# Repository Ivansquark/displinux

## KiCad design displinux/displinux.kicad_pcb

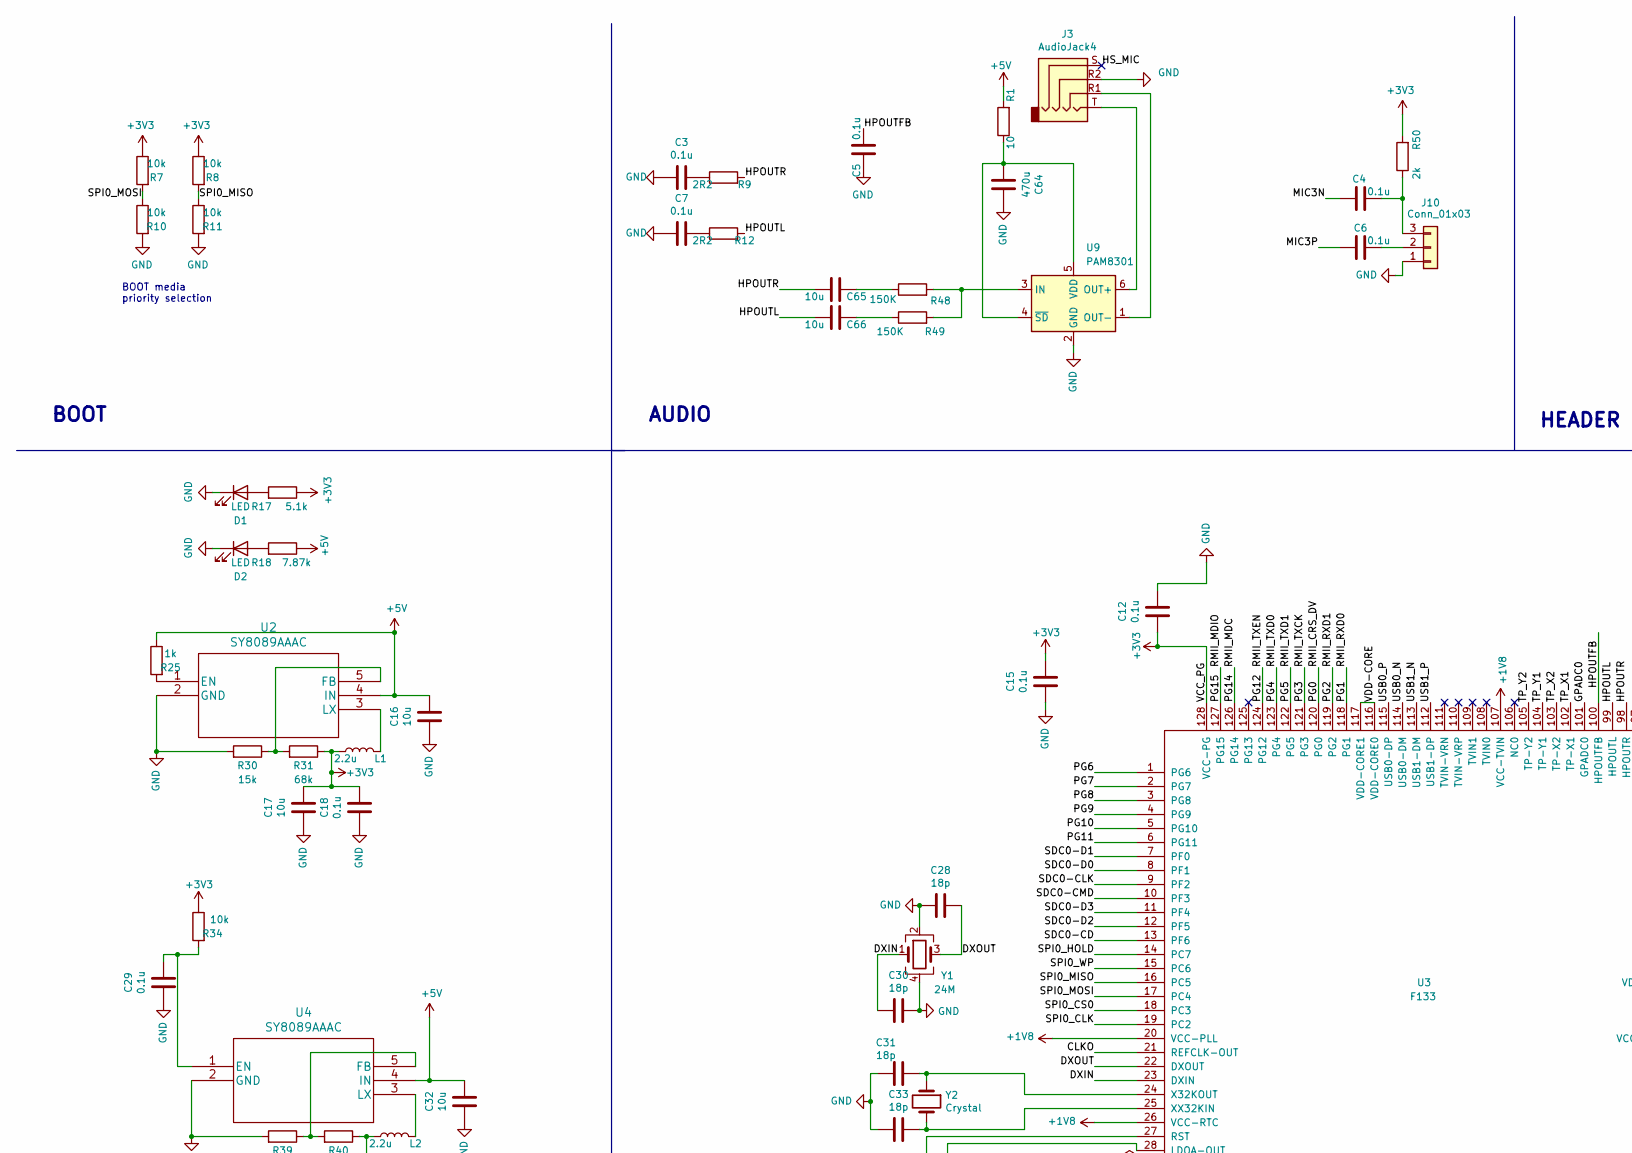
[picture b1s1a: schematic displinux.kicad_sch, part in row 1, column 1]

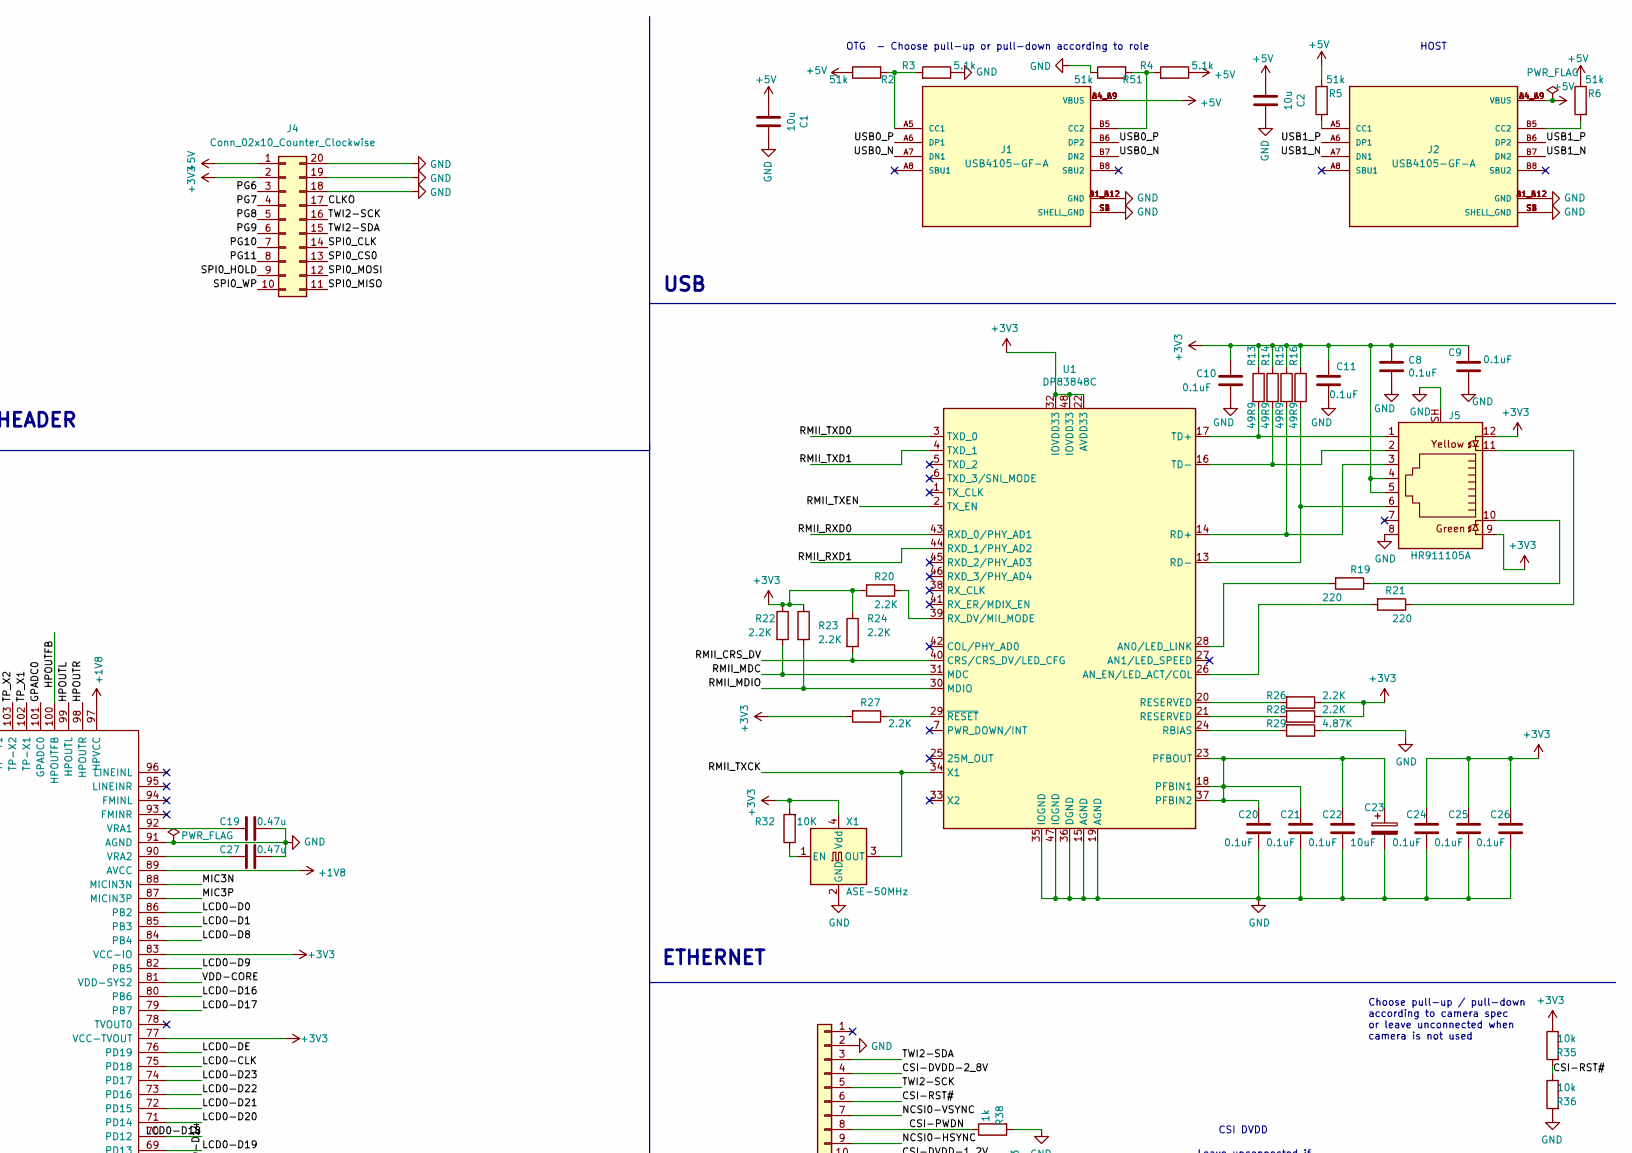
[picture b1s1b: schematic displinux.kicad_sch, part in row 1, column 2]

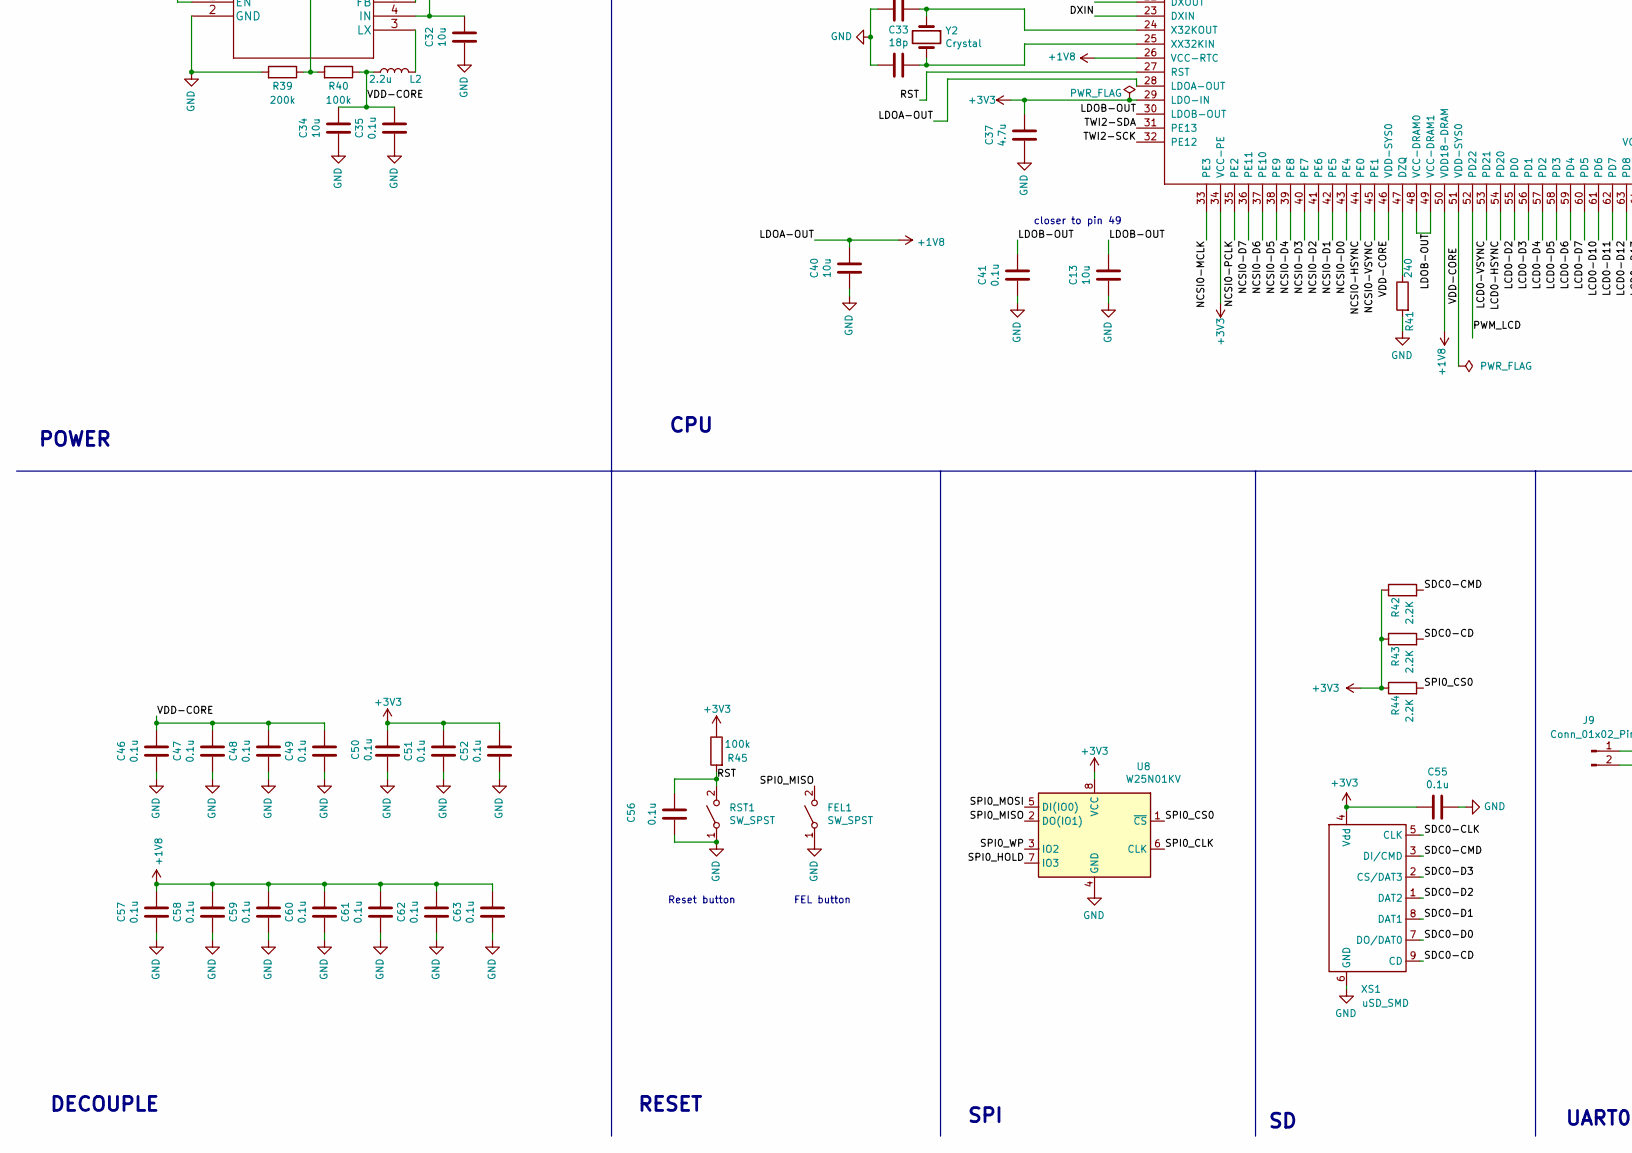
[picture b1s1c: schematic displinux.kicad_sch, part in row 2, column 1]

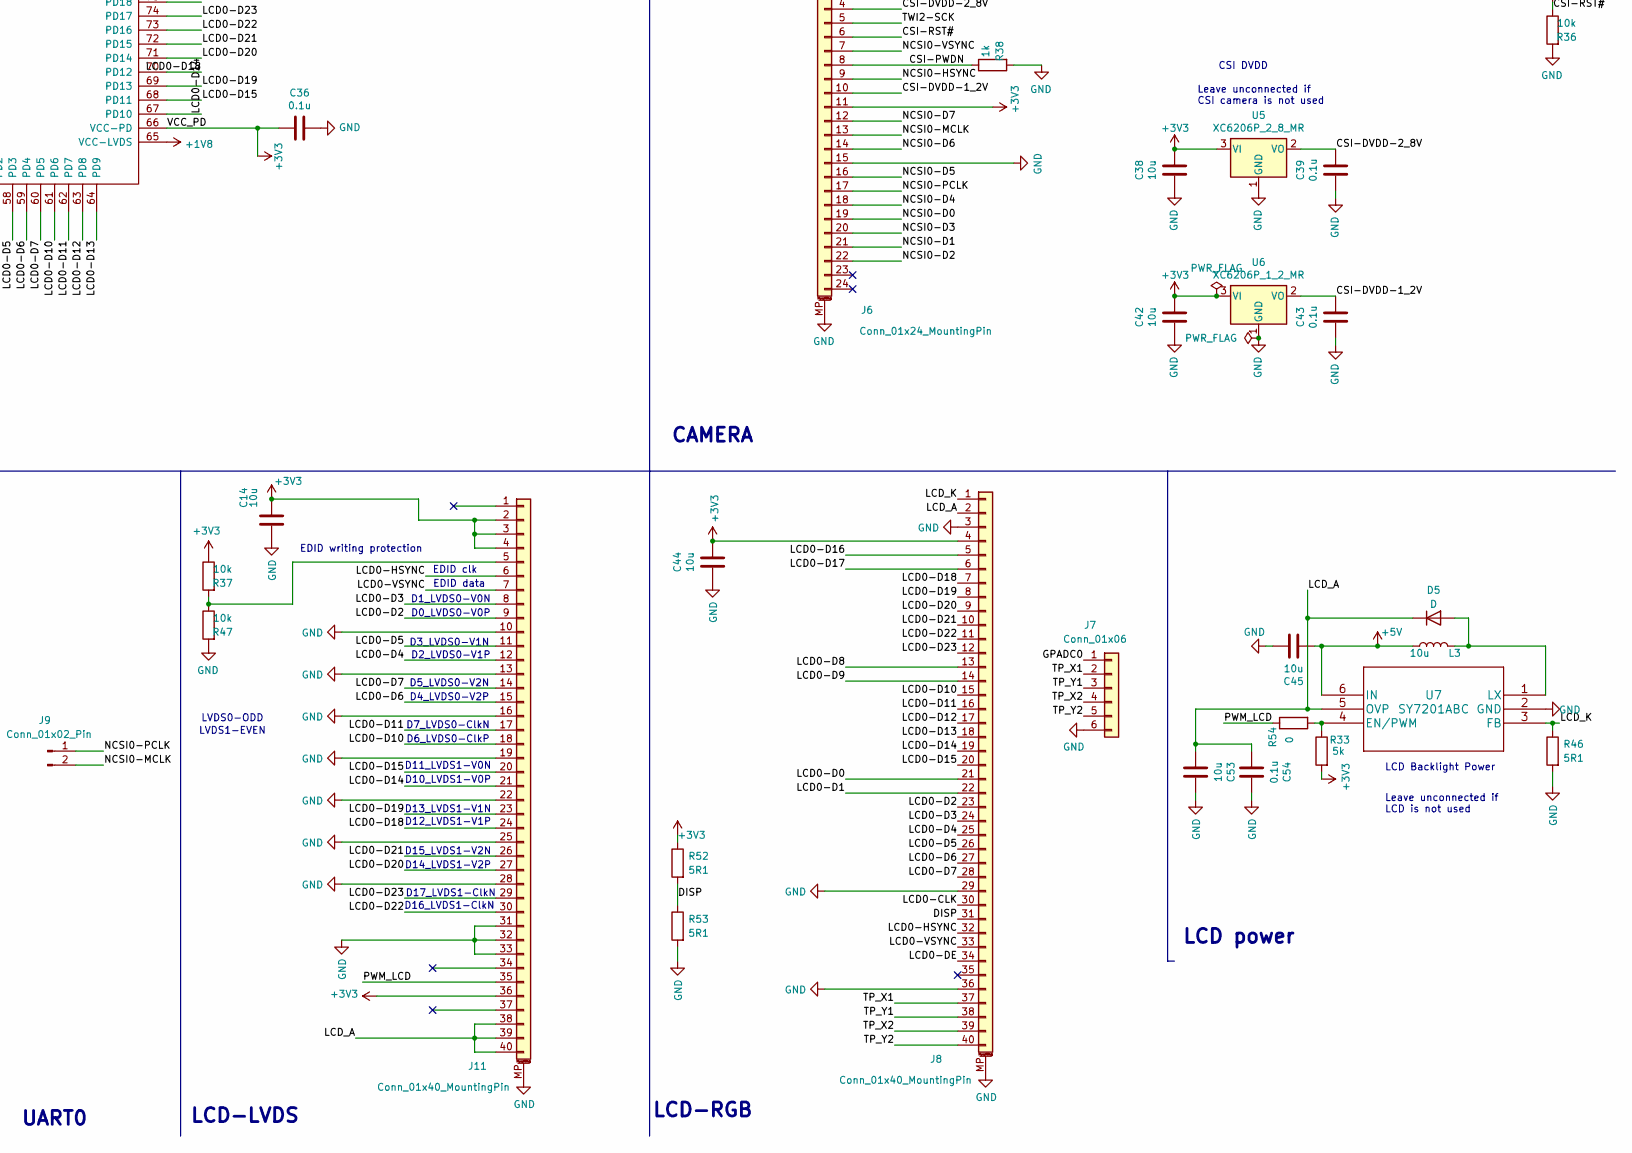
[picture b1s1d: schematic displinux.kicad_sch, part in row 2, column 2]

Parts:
C1, C2, C13, C14, C16, C17, C32, C34, C38, C40, C42, C44, C45, C53, C65, C66: 10u; C_0603_1608Metric
C3, C4, C5, C6, C7, C12, C15, C18, C29, C35, C36, C39, C41, C43, C46, C47, C48, C49, C50, C51, C52, C54, C55, C56, C57, C58, C59, C60, C61, C62, C63: 0.1u; C_0603_1608Metric
C8, C9, C10, C11, C20, C21, C22, C24, C25, C26: 0.1uF; C_0603_1608Metric
C19, C27: 0.47u; C_0603_1608Metric
C23: 10uF; CP_EIA-3216-10_Kemet-I
C28, C30, C31, C33: 18p; C_0603_1608Metric
C37: 4.7u; C_0603_1608Metric
C64: 470u; C_0603_1608Metric
D1, D2: LED; LED_0603_1608Metric
D5: D; D_2010_5025Metric
FEL1: SW_SPST; SW_SPST_EVQPE1
J1, J2: USB4105-GF-A; USB_C_Receptacle_G-Switch_GT-USB-7010ASV; PARTREV A3
J3: AudioJack4; Jack_3.5mm_PJ320D_Horizontal
J4: Conn_02x10_Counter_Clockwise; PinHeader_2x10_P2.54mm_Vertical
J5: HR911105A; RJ45_Hanrun_HR911105A_Horizontal
J6: Conn_01x24_MountingPin; TE_2-1734839-4_1x24-1MP_P0.5mm_Horizontal
J7: Conn_01x06; PinHeader_1x06_P2.54mm_Vertical
J8, J11: Conn_01x40_MountingPin; TE_4-1734839-0_1x40-1MP_P0.5mm_Horizontal
J9: Conn_01x02_Pin; PinHeader_1x02_P2.54mm_Vertical
J10: Conn_01x03; PinHeader_1x03_P2.54mm_Vertical
L1, L2: 2.2u; L_Wurth_WE-LQSH-3012
L3: 10u; L_Wurth_WE-LQSH-3012
R1: 10; R_0603_1608Metric
R2, R5, R6, R51: 51k; R_0603_1608Metric
R3, R4, R17: 5.1k; R_0603_1608Metric
R7, R8, R10, R11, R34, R35, R36, R37, R47: 10k; R_0603_1608Metric
R9, R12: 2R2; R_0603_1608Metric
R13, R14, R15, R16: 49R9; R_0603_1608Metric
R18: 7.87k; R_0603_1608Metric
R19, R21: 220; R_0603_1608Metric
R20, R22, R23, R24, R26, R27, R28, R42, R43, R44: 2.2K; R_0603_1608Metric
R25, R38: 1k; R_0603_1608Metric
R29: 4.87K; R_0805_2012Metric_Pad1.20x1.40mm_HandSolder
R30: 15k; R_0603_1608Metric
R31: 68k; R_0603_1608Metric
R32: 10K; R_0603_1608Metric
R33: 5k; R_0603_1608Metric
R39: 200k; R_0603_1608Metric
R40, R45: 100k; R_0603_1608Metric
R41: 240; R_0603_1608Metric
R46, R52, R53: 5R1; R_0603_1608Metric
R48, R49: 150K; R_0603_1608Metric
R50: 2k; R_0603_1608Metric
R54: 0; R_0603_1608Metric
RST1: SW_SPST; SW_SPST_EVQPE1
U1: DP83848C; LQFP-48_7x7mm_P0.5mm
U2, U4: SY8089AAAC; SOT-23-5
U3: F133; LQFP-128_14x14mm_P0.4mm
U5: XC6206P_2_8_MR; SOT-23
U6: XC6206P_1_2_MR; SOT-23
U7: SY7201ABC; SOT-23-6
U8: W25N01KV; WSON-8-1EP_6x5mm_P1.27mm_EP3.4x4.3mm
U9: PAM8301; SOT-23-6
X1: ASE-50MHz; Oscillator_SMD_Abracon_ASE-4Pin_3.2x2.5mm
XS1: uSD_SMD; J_SD_Card-micro_socket_A
Y1: 24M; Crystal_SMD_3225-4Pin_3.2x2.5mm
Y2: Crystal; Crystal_SMD_3215-2Pin_3.2x1.5mm

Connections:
+1V8: C40.1, C57.1, C58.1, C59.1, C60.1, C61.1, C62.1, C63.1, U3.20 (VCC-PLL), U3.26 (VCC-RTC), U3.28 (LDOA-OUT), U3.50 (VDD18-DRAM), U3.65 (VCC-LVDS), U3.89 (AVCC), U3.97 (HPVCC), U3.107 (VCC-TVIN)
+3V3: C8.1, C9.1, C10.1, C11.1, C12.2, C14.1, C15.1, C17.1, C18.1, C24.1, C25.1, C26.1, C36.2, C37.1, C38.2, C42.2, C44.1, C50.1, C51.1, C52.1, C55.1, J4.2, J5.4, J5.5, J5.9, J5.12, J6.11, J8.4, J11.2, J11.3, J11.4, J11.36, L1.1, R7.1, R8.1, R13.1, R14.1, R15.1, R16.1, R17.1, R20.2, R22.1, R23.1, R24.1, R26.1, R27.2, R28.1, R31.1, R32.2, R33.2, R34.1, R35.1, R37.1, R42.1, R43.1, R44.1, R45.1, R50.2, R52.1, U1.22 (AVDD33), U1.32 (IOVDD33), U1.48 (IOVDD33), U3.29 (LDO-IN), U3.34 (VCC-PE), U3.66 (VCC-PD), U3.77 (VCC-TVOUT), U3.83 (VCC-IO), U3.128 (VCC-PG), U5.3 (VI), U6.3 (VI), U8.8 (VCC), X1.4 (Vdd), XS1.4 (Vdd)
+5V: C1.1, C2.1, C16.1, C32.1, C45.1, J1.A4_B9 (VBUS), J1.B4_A9 (VBUS), J2.A4_B9 (VBUS), J2.B4_A9 (VBUS), J4.1, L3.1, R1.2, R2.1, R4.1, R5.1, R6.1, R18.1, R25.1, U2.4 (IN), U4.4 (IN), U7.6 (IN)
/CLKO: J4.17, U3.21 (REFCLK-OUT)
/CSI-DVDD-1_2V: C43.1, J6.10, U6.2 (VO)
/CSI-DVDD-2_8V: C39.1, J6.4, U5.2 (VO)
/CSI-PWDN: J6.8, R38.1
/CSI-RST#: J6.6, R35.2, R36.1
/DISP: J8.31, R52.2, R53.1
/DXIN: C30.2, U3.23 (DXIN), Y1.1
/DXOUT: C28.1, U3.22 (DXOUT), Y1.3
/GPADC0: J7.1, U3.101 (GPADC0)
/HPOUTFB: C5.1, U3.100 (HPOUTFB)
/HPOUTL: C66.1, R12.2, U3.99 (HPOUTL)
/HPOUTR: C65.1, R9.2, U3.98 (HPOUTR)
/HS_MIC: J3.S
/LCD0-CLK: J8.30, U3.75 (PD18)
/LCD0-D0: J8.21, U3.86 (PB2)
/LCD0-D1: J8.22, U3.85 (PB3)
/LCD0-D2: J8.23, J11.9, U3.55 (PD0)
/LCD0-D3: J8.24, J11.8, U3.56 (PD1)
/LCD0-D4: J8.25, J11.12, U3.57 (PD2)
/LCD0-D5: J8.26, J11.11, U3.58 (PD3)
/LCD0-D6: J8.27, J11.15, U3.59 (PD4)
/LCD0-D7: J8.28, J11.14, U3.60 (PD5)
/LCD0-D8: J8.13, U3.84 (PB4)
/LCD0-D9: J8.14, U3.82 (PB5)
/LCD0-D10: J8.15, J11.18, U3.61 (PD6)
/LCD0-D11: J8.16, J11.17, U3.62 (PD7)
/LCD0-D12: J8.17, U3.63 (PD8)
/LCD0-D13: J8.18, U3.64 (PD9)
/LCD0-D14: J8.19, J11.21, U3.67 (PD10)
/LCD0-D15: J8.20, J11.20, U3.68 (PD11)
/LCD0-D16: J8.5, U3.80 (PB6)
/LCD0-D17: J8.6, U3.79 (PB7)
/LCD0-D18: J8.7, J11.24, U3.70 (PD12)
/LCD0-D19: J8.8, J11.23, U3.69 (PD13)
/LCD0-D20: J8.9, J11.27, U3.71 (PD14)
/LCD0-D21: J8.10, J11.26, U3.72 (PD15)
/LCD0-D22: J8.11, J11.30, U3.73 (PD16)
/LCD0-D23: J8.12, J11.29, U3.74 (PD17)
/LCD0-DE: J8.34, U3.76 (PD19)
/LCD0-HSYNC: J8.32, J11.6, U3.54 (PD20)
/LCD0-VSYNC: J8.33, J11.7, U3.53 (PD21)
/LCD_A: C53.1, C54.1, D5.1 (K), J8.2, J11.38, J11.39, J11.40, U7.5 (OVP)
/LCD_K: J8.1, R46.1, U7.3 (FB)
/LDOB-OUT: C13.1, C41.1, U3.30 (LDOB-OUT), U3.48 (VCC-DRAM0), U3.49 (VCC-DRAM1)
/MIC3N: C4.1, U3.88 (MICIN3N)
/MIC3P: C6.1, U3.87 (MICIN3P)
/NCSI0-D0: J6.19, U3.43 (PE4)
/NCSI0-D1: J6.21, U3.42 (PE5)
/NCSI0-D2: J6.22, U3.41 (PE6)
/NCSI0-D3: J6.20, U3.40 (PE7)
/NCSI0-D4: J6.18, U3.39 (PE8)
/NCSI0-D5: J6.16, U3.38 (PE9)
/NCSI0-D6: J6.14, U3.37 (PE10)
/NCSI0-D7: J6.12, U3.36 (PE11)
/NCSI0-HSYNC: J6.9, U3.44 (PE0)
/NCSI0-MCLK: J6.13, J9.2, U3.33 (PE3)
/NCSI0-PCLK: J6.17, J9.1, U3.35 (PE2)
/NCSI0-VSYNC: J6.7, U3.45 (PE1)
/PG0: R24.2, U1.40 (CRS/CRS_DV/LED_CFG), U3.120 (PG0)
/PG1: U1.43 (RXD_0/PHY_AD1), U3.118 (PG1)
/PG2: U1.44 (RXD_1/PHY_AD2), U3.119 (PG2)
/PG3: U1.34 (X1), U3.121 (PG3), X1.3 (OUT)
/PG4: U1.3 (TXD_0), U3.123 (PG4)
/PG5: U1.4 (TXD_1), U3.122 (PG5)
/PG6: J4.3, U3.1 (PG6)
/PG7: J4.4, U3.2 (PG7)
/PG8: J4.5, U3.3 (PG8)
/PG9: J4.6, U3.4 (PG9)
/PG10: J4.7, U3.5 (PG10)
/PG11: J4.8, U3.6 (PG11)
/PG12: U1.2 (TX_EN), U3.124 (PG12)
/PG14: R22.2, U1.31 (MDC), U3.126 (PG14)
/PG15: R23.2, U1.30 (MDIO), U3.127 (PG15)
/PWM_LCD: J11.35, R54.1, U3.52 (PD22)
/RST: C56.1, R45.2, RST1.2 (B), U3.27 (RST)
/SDC0-CD: R43.2, U3.13 (PF6), XS1.9 (CD)
/SDC0-CLK: U3.9 (PF2), XS1.5 (CLK)
/SDC0-CMD: R42.2, U3.10 (PF3), XS1.3 (DI/CMD)
/SDC0-D0: U3.8 (PF1), XS1.7 (DO/DAT0)
/SDC0-D1: U3.7 (PF0), XS1.8 (DAT1)
/SDC0-D2: U3.12 (PF5), XS1.1 (DAT2)
/SDC0-D3: U3.11 (PF4), XS1.2 (CS/DAT3)
/SPI0_CLK: J4.14, U3.19 (PC2), U8.6 (CLK)
/SPI0_CS0: J4.13, R44.2, U3.18 (PC3), U8.1 (~CS)
/SPI0_HOLD: J4.9, U3.14 (PC7), U8.7 (IO3)
/SPI0_MISO: FEL1.2 (B), J4.11, R8.2, R11.1, U3.16 (PC5), U8.2 (DO(IO1))
/SPI0_MOSI: J4.12, R7.2, R10.1, U3.17 (PC4), U8.5 (DI(IO0))
/SPI0_WP: J4.10, U3.15 (PC6), U8.3 (IO2)
/TP_X1: J7.2, J8.37, U3.102 (TP-X1)
/TP_X2: J7.4, J8.39, U3.103 (TP-X2)
/TP_Y1: J7.3, J8.38, U3.104 (TP-Y1)
/TP_Y2: J7.5, J8.40, U3.105 (TP-Y2)
/TWI2-SCK: J4.16, J6.5, U3.32 (PE12)
/TWI2-SDA: J4.15, J6.3, U3.31 (PE13)
/USB0_N: J1.A7 (DN1), J1.B7 (DN2), U3.114 (USB0-DM)
/USB0_P: J1.A6 (DP1), J1.B6 (DP2), U3.115 (USB0-DP)
/USB1_N: J2.A7 (DN1), J2.B7 (DN2), U3.113 (USB1-DM)
/USB1_P: J2.A6 (DP1), J2.B6 (DP2), U3.112 (USB1-DP)
/VDD-CORE: C34.1, C35.1, C46.1, C47.1, C48.1, C49.1, L2.1, R40.1, U3.46 (VDD-SYS0), U3.51 (VDD-SYS0), U3.81 (VDD-SYS2), U3.116 (VDD-CORE0), U3.117 (VDD-CORE1)
GND: C1.2, C2.2, C3.1, C5.2, C7.1, C8.2, C9.2, C10.2, C11.2, C12.1, C13.2, C14.2, C15.2, C16.2, C17.2, C18.2, C19.1, C20.2, C21.2, C22.2, C23.2, C24.2, C25.2, C26.2, C27.1, C28.2, C29.2, C30.1, C31.2, C32.2, C33.2, C34.2, C35.2, C36.1, C37.2, C38.1, C39.2, C40.2, C41.2, C42.1, C43.2, C44.2, C45.2, C46.2, C47.2, C48.2, C49.2, C50.2, C51.2, C52.2, C53.2, C54.2, C55.2, C56.2, C57.2, C58.2, C59.2, C60.2, C61.2, C62.2, C63.2, C64.2, D1.1 (K), D2.1 (K), FEL1.1 (A), J1.A1_B12 (GND), J1.B1_A12 (GND), J1.S1 (SHELL_GND), J1.S2 (SHELL_GND), J1.S3 (SHELL_GND), J1.S4 (SHELL_GND), J2.A1_B12 (GND), J2.B1_A12 (GND), J2.S1 (SHELL_GND), J2.S2 (SHELL_GND), J2.S3 (SHELL_GND), J2.S4 (SHELL_GND), J3.R2, J4.18, J4.19, J4.20, J5.8, J5.SH, J6.2, J6.15, J6.MP (MountPin), J7.6, J8.3, J8.29, J8.36, J8.MP (MountPin), J10.1, J11.10, J11.13, J11.16, J11.19, J11.22, J11.25, J11.28, J11.31, J11.32, J11.33, J11.MP (MountPin), R3.1, R10.2, R11.2, R29.1, R30.2, R36.2, R38.2, R39.2, R41.2, R46.2, R47.2, R51.1, R53.2, RST1.1 (A), U1.15 (AGND), U1.19 (AGND), U1.35 (IOGND), U1.36 (DGND), U1.47 (IOGND), U2.2 (GND), U3.91 (AGND), U4.2 (GND), U5.1 (GND), U6.1 (GND), U7.2 (GND), U8.4 (GND), U9.2 (GND), X1.2 (GND), XS1.6 (GND), XS1.SH, Y1.2, Y1.4
unnamed: C3.2, R9.1
unnamed: C7.2, R12.1
unnamed: C65.2, R48.1
unnamed: C66.2, R49.1
unnamed: D1.2 (A), R17.2
unnamed: D2.2 (A), R18.2
unnamed: D5.2 (A), L3.2, U7.1 (LX)
unnamed: J1.A5 (CC1), R2.2, R3.2
unnamed: J1.B5 (CC2), R4.2, R51.2
unnamed: J2.A5 (CC1), R5.2
unnamed: J2.B5 (CC2), R6.2
unnamed: J5.10, R19.1
unnamed: J5.11, R21.1
unnamed: C6.2, J10.2
unnamed: C4.2, J10.3, R50.1
unnamed: J11.5, R37.2, R47.1
unnamed: R26.2, U1.20 (RESERVED)
unnamed: R28.2, U1.21 (RESERVED)
unnamed: R19.2, U1.28 (AN0/LED_LINK)
unnamed: R21.2, U1.26 (AN_EN/LED_ACT/COL)
unnamed: C20.1, C21.1, C22.1, C23.1, U1.18 (PFBIN1), U1.23 (PFBOUT), U1.37 (PFBIN2)
unnamed: R29.2, U1.24 (RBIAS)
unnamed: J5.3, R15.2, U1.14 (RD+)
unnamed: J5.6, R16.2, U1.13 (RD-)
unnamed: R20.1, U1.39 (RX_DV/MII_MODE)
unnamed: J5.1, R13.2, U1.17 (TD+)
unnamed: J5.2, R14.2, U1.16 (TD-)
unnamed: R27.1, U1.29 (~RESET)
unnamed: R25.2, U2.1 (EN)
unnamed: R30.1, R31.2, U2.5 (FB)
unnamed: L1.2, U2.3 (LX)
unnamed: R41.1, U3.47 (DZQ)
unnamed: C19.2, U3.92 (VRA1)
unnamed: C27.2, U3.90 (VRA2)
unnamed: C31.1, U3.24 (X32KOUT), Y2.1
unnamed: C33.1, U3.25 (XX32KIN), Y2.2
unnamed: C29.1, R34.2, U4.1 (EN)
unnamed: R39.1, R40.2, U4.5 (FB)
unnamed: L2.2, U4.3 (LX)
unnamed: R33.1, R54.2, U7.4 (EN/PWM)
unnamed: R48.2, R49.2, U9.3 (IN)
unnamed: J3.T, U9.6 (OUT+)
unnamed: J3.R1, U9.1 (OUT-)
unnamed: C64.1, R1.1, U9.4 (~SD), U9.5 (VDD)
unnamed: R32.1, X1.1 (EN)

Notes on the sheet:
USB
BOOT
SPI
D10_LVDS1-V0P
closer to pin 49
LVDS1-EVEN
D11_LVDS1-V0N
D1_LVDS0-V0N
HOST
D4_LVDS0-V2P
CAMERA
D0_LVDS0-V0P
EDID clk
D3_LVDS0-V1N
D17_LVDS1-ClkN
D5_LVDS0-V2N
Choose pull-up / pull-down according to camera spec or leave unconnected when camera is not used
Leave unconnected if LCD is not used
D2_LVDS0-V1P
D13_LVDS1-V1N
D12_LVDS1-V1P
CSI DVDD
D15_LVDS1-V2N
D6_LVDS0-ClkP
DECOUPLE
LCD-LVDS
EDID writing protection
UART0
BOOT media priority selection
HEADER
POWER
LCD-RGB
FEL button
D16_LVDS1-ClkN
D14_LVDS1-V2P
D7_LVDS0-ClkN
OTG - Choose pull-up or pull-down according to role
EDID data
LCD power
LCD Backlight Power

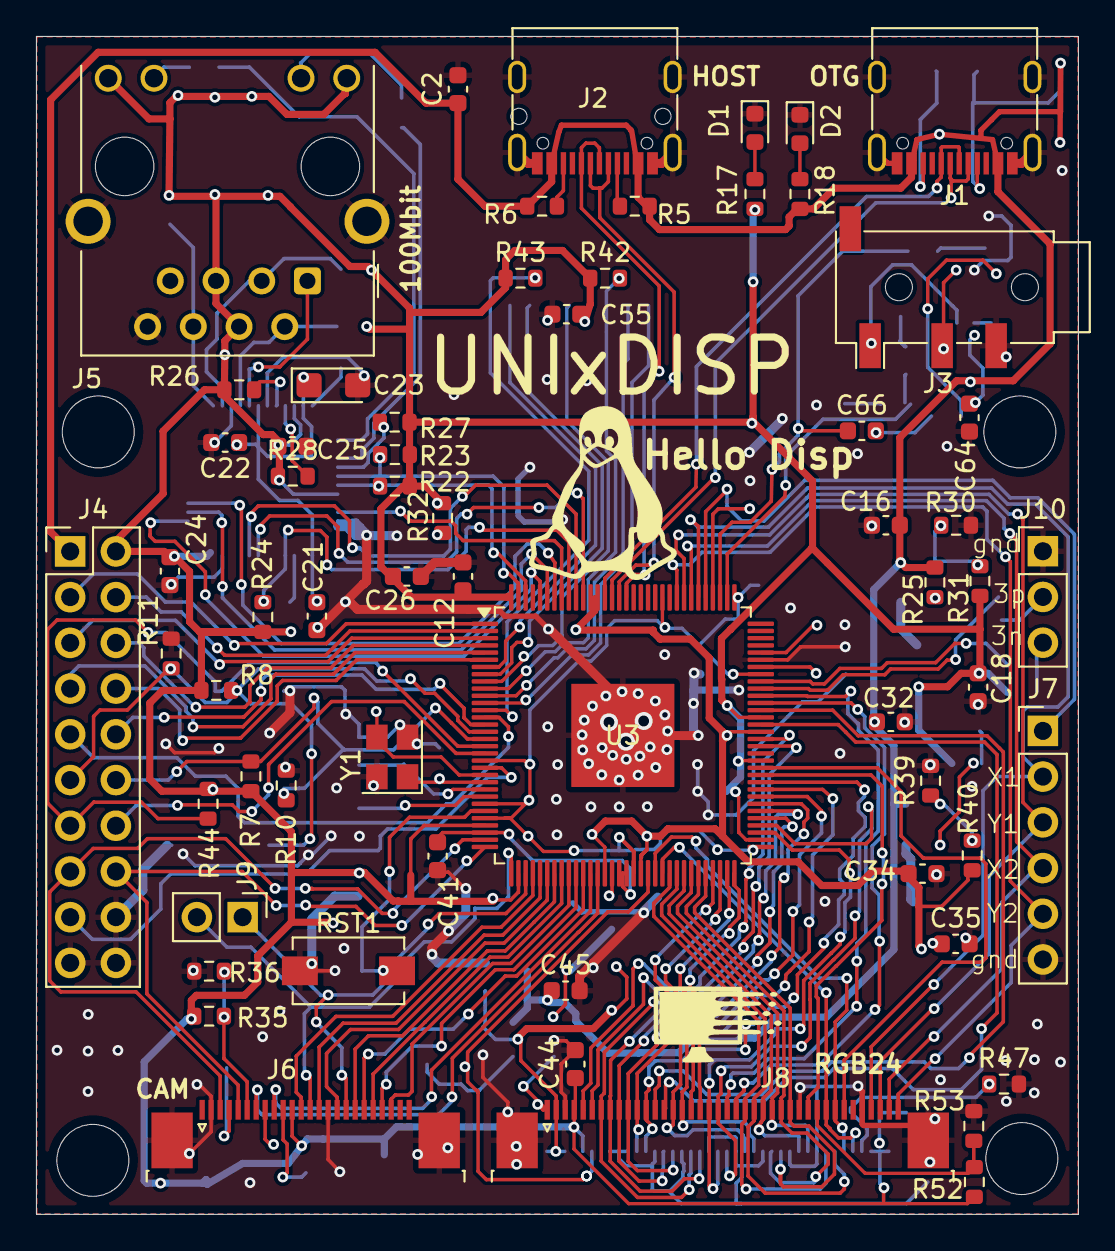
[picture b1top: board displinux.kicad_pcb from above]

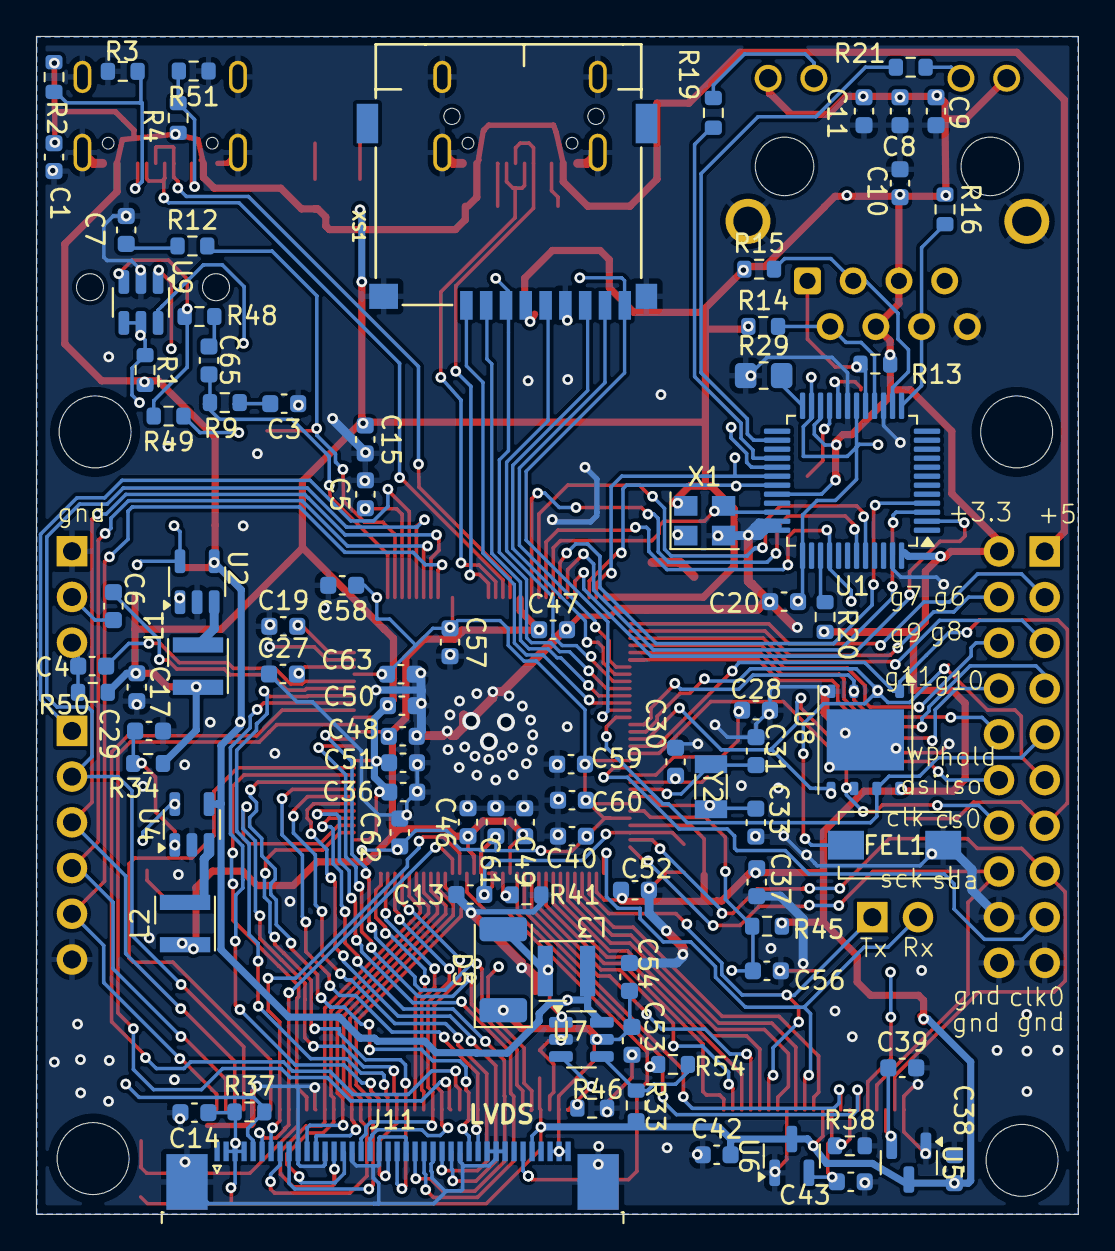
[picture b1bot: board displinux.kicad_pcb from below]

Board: 2 copper layers, 57.9 x 65.4 mm, 153 parts (90 on the bottom side), 147 nets.

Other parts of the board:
Hello Disp: LOGO; linux_mascot

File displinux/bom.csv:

Reference,Value,Footprint,Qty
"C1,C2,C16,C17,C32,C34,C38,C42,C45,C53,L3",10u,-- смешанные значения --,11
"C3,C4,C5,C6,C7,C12,C15,C18,C29,C35,C36,C37,C39,C40,C41,C43,",0.1u,Capacitor_SMD:C_0603_1608Metric,34
"C44,C46,C47,C48,C49,C50,C51,C52,C54,C55,C56,C57,C58,C59,C60,C61,C62,C63",0.1u,Capacitor_SMD:C_0603_1608Metric,
"C8,C9,C10,C11,C20,C21,C22,C24,C25,C26",0.1uF,Capacitor_SMD:C_0603_1608Metric,10
"C19,C27",0.47u,Capacitor_SMD:C_0603_1608Metric,2
C23,10uF,Capacitor_Tantalum_SMD:CP_EIA-3216-10_Kemet-I,1
"C28,C30,C31,C33",18p,Capacitor_SMD:C_0603_1608Metric,4
"D1,D2",LED,LED_SMD:LED_0603_1608Metric,2
"D3,D5",D,-- смешанные значения --,2
"FEL1,RST1",SW_SPST,Button_Switch_SMD:SW_SPST_EVQPE1,2
"J1,J2",USB4105-GF-A,Connector_USB:USB_C_Receptacle_G-Switch_GT-USB-7010ASV,2
J3,AudioJack4,Connector_Audio:Jack_3.5mm_PJ320D_Horizontal,1
J4,Conn_02x10_Counter_Clockwise,Connector_PinHeader_2.54mm:PinHeader_2x10_P2.54mm_Vertical,1
J5,HR911105A,Connector_RJ:RJ45_Hanrun_HR911105A_Horizontal,1
J6,Conn_01x24_MountingPin,Connector_FFC-FPC:TE_2-1734839-4_1x24-1MP_P0.5mm_Horizontal,1
J7,Conn_01x06,Connector_PinHeader_2.54mm:PinHeader_1x06_P2.54mm_Vertical,1
J8,Conn_01x40_MountingPin,Connector_FFC-FPC:TE_4-1734839-0_1x40-1MP_P0.5mm_Horizontal,1
J9,Conn_01x02_Pin,Connector_PinHeader_2.54mm:PinHeader_1x02_P2.54mm_Vertical,1
J10,Conn_01x03,Connector_PinHeader_2.54mm:PinHeader_1x03_P2.54mm_Vertical,1
"L1,L2",2.2u,Inductor_SMD_Wurth:L_Wurth_WE-LQSH-3012,2
"R1,R2,R3,R4,R5,R6,R17",5.1k,Resistor_SMD:R_0603_1608Metric,7
"R7,R8,R10,R11,R34,R35,R36,R47,R48,R49,R50,R51,R52,R53,R54",10k,Resistor_SMD:R_0603_1608Metric,15
"R9,R12,R46",2R2,Resistor_SMD:R_0603_1608Metric,3
"R13,R14,R15,R16",49R9,Resistor_SMD:R_0603_1608Metric,4
R18,7.87k,Resistor_SMD:R_0603_1608Metric,1
"R19,R21",220,Resistor_SMD:R_0603_1608Metric,2
"R20,R22,R23,R24,R26,R27,R28,R42,R43,R44",2.2K,Resistor_SMD:R_0603_1608Metric,10
"R25,R38",1k,Resistor_SMD:R_0603_1608Metric,2
R29,4.87K,Resistor_SMD:R_0603_1608Metric,1
R30,15k,Resistor_SMD:R_0603_1608Metric,1
R31,68k,Resistor_SMD:R_0603_1608Metric,1
R32,10K,Resistor_SMD:R_0603_1608Metric,1
R33,0,Resistor_SMD:R_0603_1608Metric,1
R39,200k,Resistor_SMD:R_0603_1608Metric,1
"R40,R45",100k,Resistor_SMD:R_0603_1608Metric,2
R41,240,Resistor_SMD:R_0603_1608Metric,1
U1,DP83848C,Package_QFP:LQFP-48_7x7mm_P0.5mm,1
"U2,U4",SY8089AAAC,Package_TO_SOT_SMD:SOT-23-5,2
U3,F133,Package_QFP:LQFP-128_14x14mm_P0.4mm,1
U5,XC6206P_2_8_MR,Package_TO_SOT_SMD:SOT-23,1
U6,XC6206P_1_2_MR,Package_TO_SOT_SMD:SOT-23,1
U7,SY7201ABC,Package_TO_SOT_SMD:SOT-23-6,1
U8,W25N01KV,Package_SON:WSON-8-1EP_6x5mm_P1.27mm_EP3.4x4.3mm,1
X1,ASE-50MHz,Oscillator:Oscillator_SMD_Abracon_ASE-4Pin_3.2x2.5mm,1
XS1,uSD_SMD,Connector_Card:microSD_HC_Hirose_DM3AT-SF-PEJM5,1
Y1,24M,Crystal:Crystal_SMD_3225-4Pin_3.2x2.5mm,1
Y2,Crystal,Crystal:Crystal_SMD_3215-2Pin_3.2x1.5mm,1

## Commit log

2024-07-05 add reference schematic and datasheet
2024-07-08 add schematic
2024-07-12 start tracing
2024-07-15 tracing finished Need to check
2024-07-15 add some earth
2024-08-02 add fabric files
2024-08-13 add fixes
2024-08-14 fix display power
2024-08-22 add lvds
2024-08-29 some fixes
2024-10-01 fix audio
2024-11-26 change otg CCM1 CCM2 res
2024-12-24 add GND SD
